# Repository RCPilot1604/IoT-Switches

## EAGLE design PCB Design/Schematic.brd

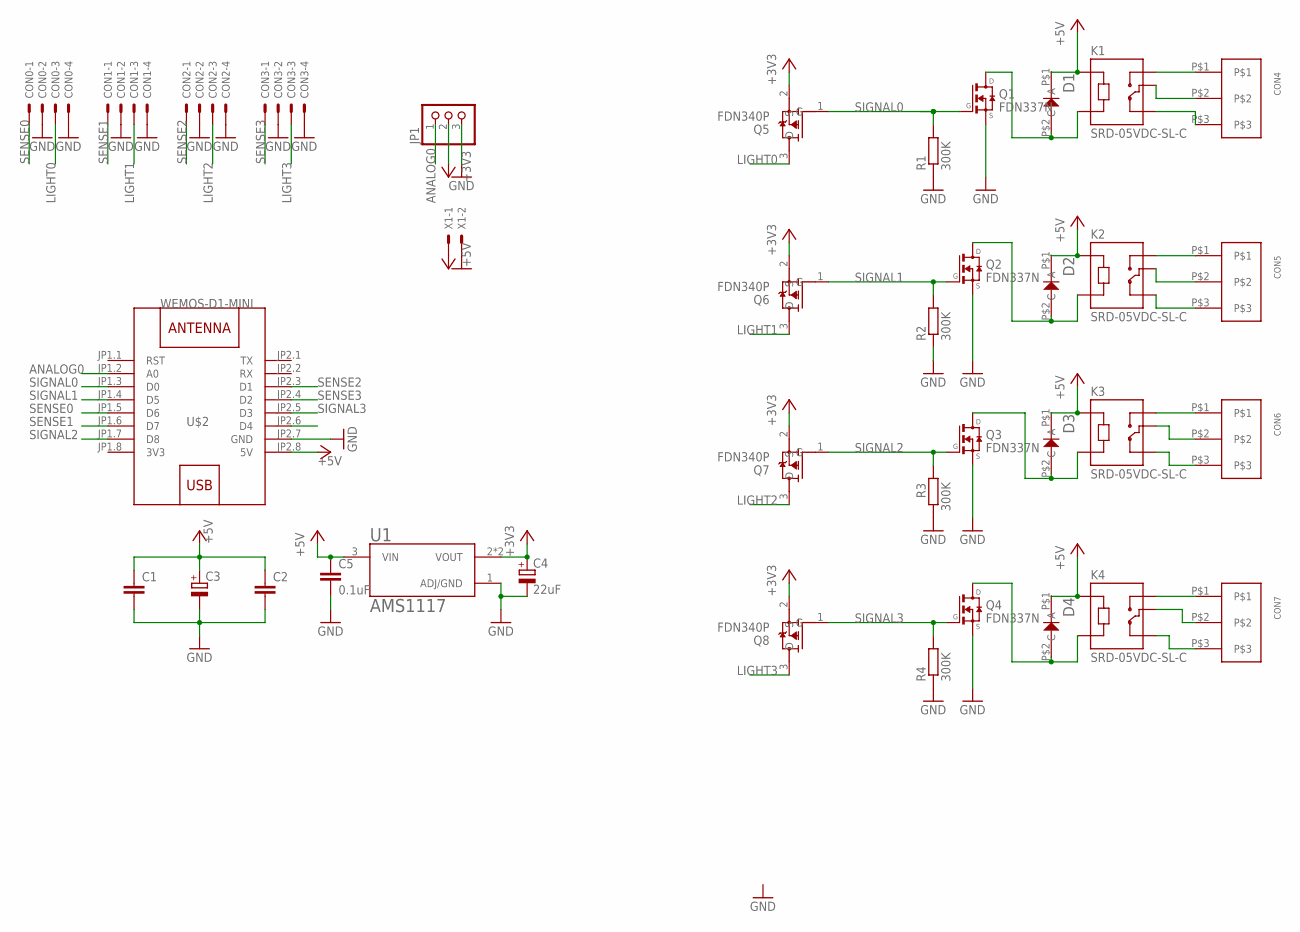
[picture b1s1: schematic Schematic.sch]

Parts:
C1, C2: C-EUC0603; C0603
C3: CPOL-EUB; PANASONIC_B
C4: 22uF; C/6032-28R
C5: 0.1uF; C0603
CON0, CON1, CON2, CON3: JST-XH-04-PIN-LONG-PAD; JST-XH-04-PACKAGE-LONG-PAD
CON4, CON5, CON6, CON7: KF-301-3P; STD
D1, D2, D3, D4: M7
JP1: PINHD-1X3; 1X03
K1, K2, K3, K4: SRD-05VDC-SL-C; RELAY_SRD-05VDC-SL-C
Q1, Q2, Q3, Q4: FDN337N; SSOT-3
Q5, Q6, Q7, Q8: FDN340P; SOT95P240X120-3N
R1, R2, R3, R4: 300K; R1206
U1: AMS1117; SOT229P700X180-4N
U$2: WEMOS-D1-MINI
X1: JST-XH-02-PIN-LONG-PAD; JST-XH-02-PACKAGE-LONG-PAD

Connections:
3V3: U$2.JP1.8 (3V3)
+3V3: C4.+, JP1.2, Q5.2 (S), Q6.2 (S), Q7.2 (S), Q8.2 (S), U1.2 (VOUT), U1.4 (VOUT)
+5V: C1.1, C2.1, C3.+, C5.1, D1.P$1 (C), D2.P$1 (C), D3.P$1 (C), D4.P$1 (C), K1.A1, K2.A1, K3.A1, K4.A1, U1.3 (VIN), U$2.JP2.8 (5V), X1.1
ANALOG0: JP1.1, U$2.JP1.2 (A0)
GND: C1.2, C2.2, C3.-, C4.-, C5.2, CON0.2, CON0.4, CON1.2, CON1.4, CON2.2, CON2.4, CON3.2, CON3.4, JP1.3, Q1.2 (S), Q2.2 (S), Q3.2 (S), Q4.2 (S), R1.1, R2.1, R3.1, R4.1, U1.1 (ADJ/GND), U$2.JP2.7 (GND), X1.2
LIGHT0: CON0.3, Q5.3 (D)
LIGHT1: CON1.3, Q6.3 (D)
LIGHT2: CON2.3, Q7.3 (D)
LIGHT3: CON3.3, Q8.3 (D)
unnamed: CON5.P$2, K2.COM
unnamed: CON4.P$1, K1.NO
unnamed: CON4.P$2, K1.COM
unnamed: D1.P$2 (A), K1.A2, Q1.3 (D)
unnamed: CON4.P$3, K1.NC
unnamed: D2.P$2 (A), K2.A2, Q2.3 (D)
unnamed: CON5.P$3, K2.NC
unnamed: CON5.P$1, K2.NO
unnamed: CON6.P$1, K3.NO
unnamed: CON6.P$2, K3.COM
unnamed: CON6.P$3, K3.NC
unnamed: CON7.P$1, K4.NO
unnamed: CON7.P$2, K4.COM
unnamed: CON7.P$3, K4.NC
unnamed: D4.P$2 (A), K4.A2, Q4.3 (D)
unnamed: D3.P$2 (A), K3.A2, Q3.3 (D)
SENSE0: CON0.1, U$2.JP1.5 (D6)
SENSE1: CON1.1, U$2.JP1.6 (D7)
SENSE2: CON2.1, U$2.JP2.3 (D1)
SENSE3: CON3.1, U$2.JP2.4 (D2)
SIGNAL0: Q1.1 (G), Q5.1 (G), R1.2, U$2.JP1.3 (D0)
SIGNAL1: Q2.1 (G), Q6.1 (G), R2.2, U$2.JP1.4 (D5)
SIGNAL2: Q3.1 (G), Q7.1 (G), R3.2, U$2.JP1.7 (D8)
SIGNAL3: Q4.1 (G), Q8.1 (G), R4.2, U$2.JP2.5 (D3)

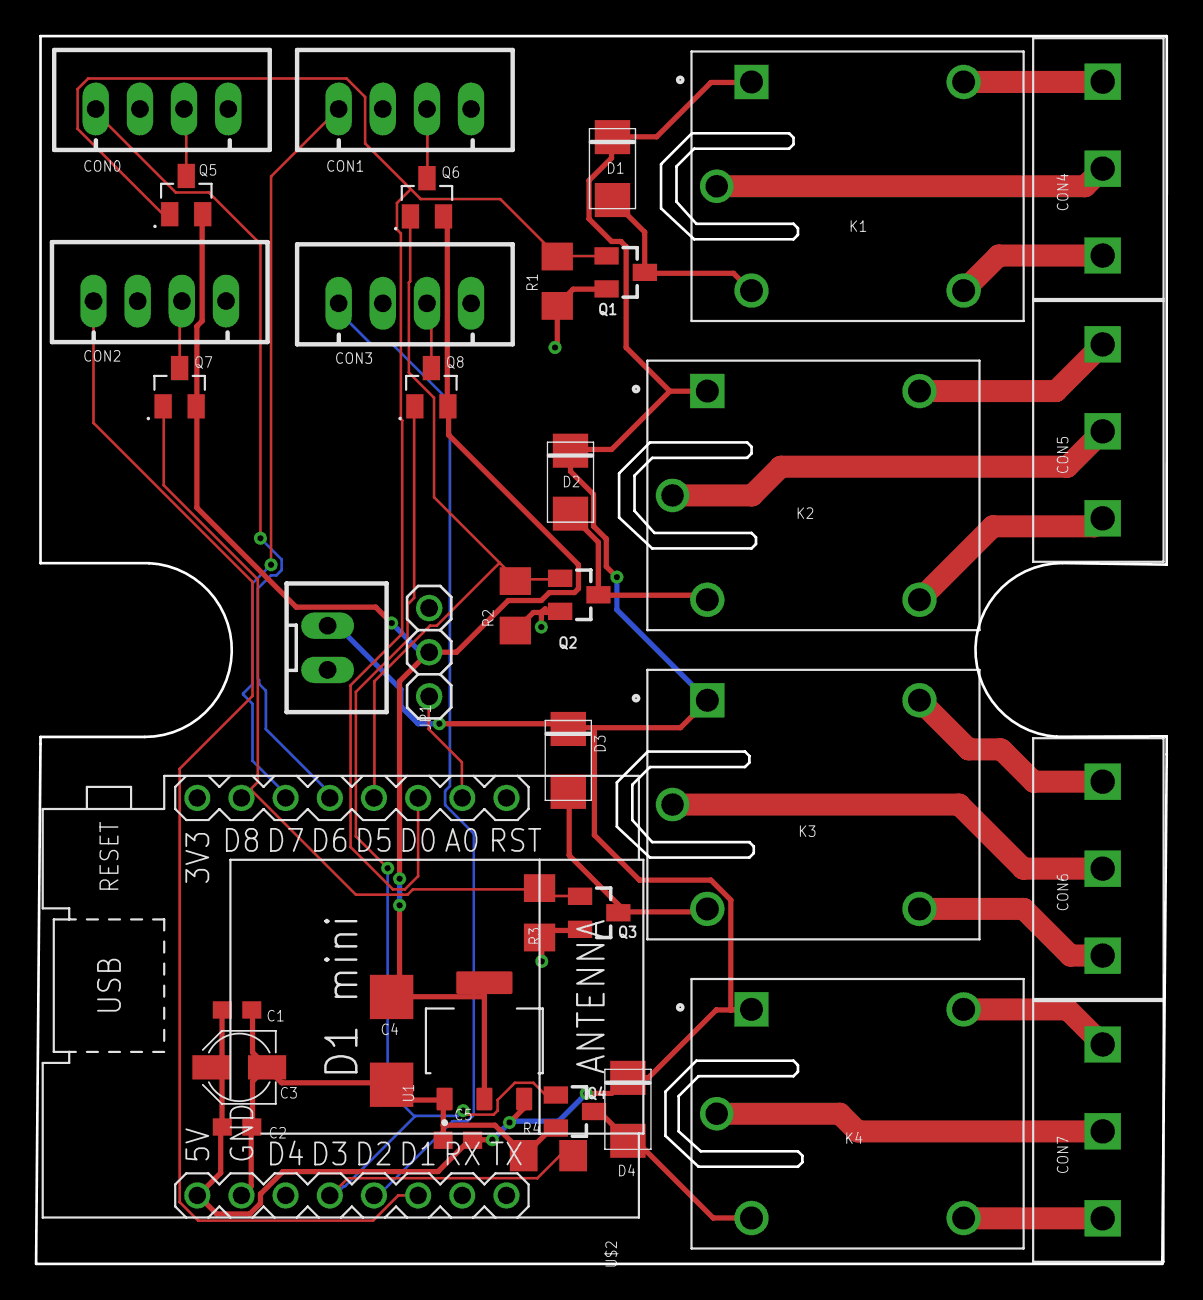
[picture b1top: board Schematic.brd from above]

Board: 2 copper layers, 65.0 x 70.6 mm, 37 parts (0 on the bottom side), 32 nets.

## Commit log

2022-12-29 Added files

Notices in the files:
parts and their libraries:
diy-modules: Released under the Creative Commons Attribution 4.0 International License: http://creativecommons.org/licenses/by/4.0
